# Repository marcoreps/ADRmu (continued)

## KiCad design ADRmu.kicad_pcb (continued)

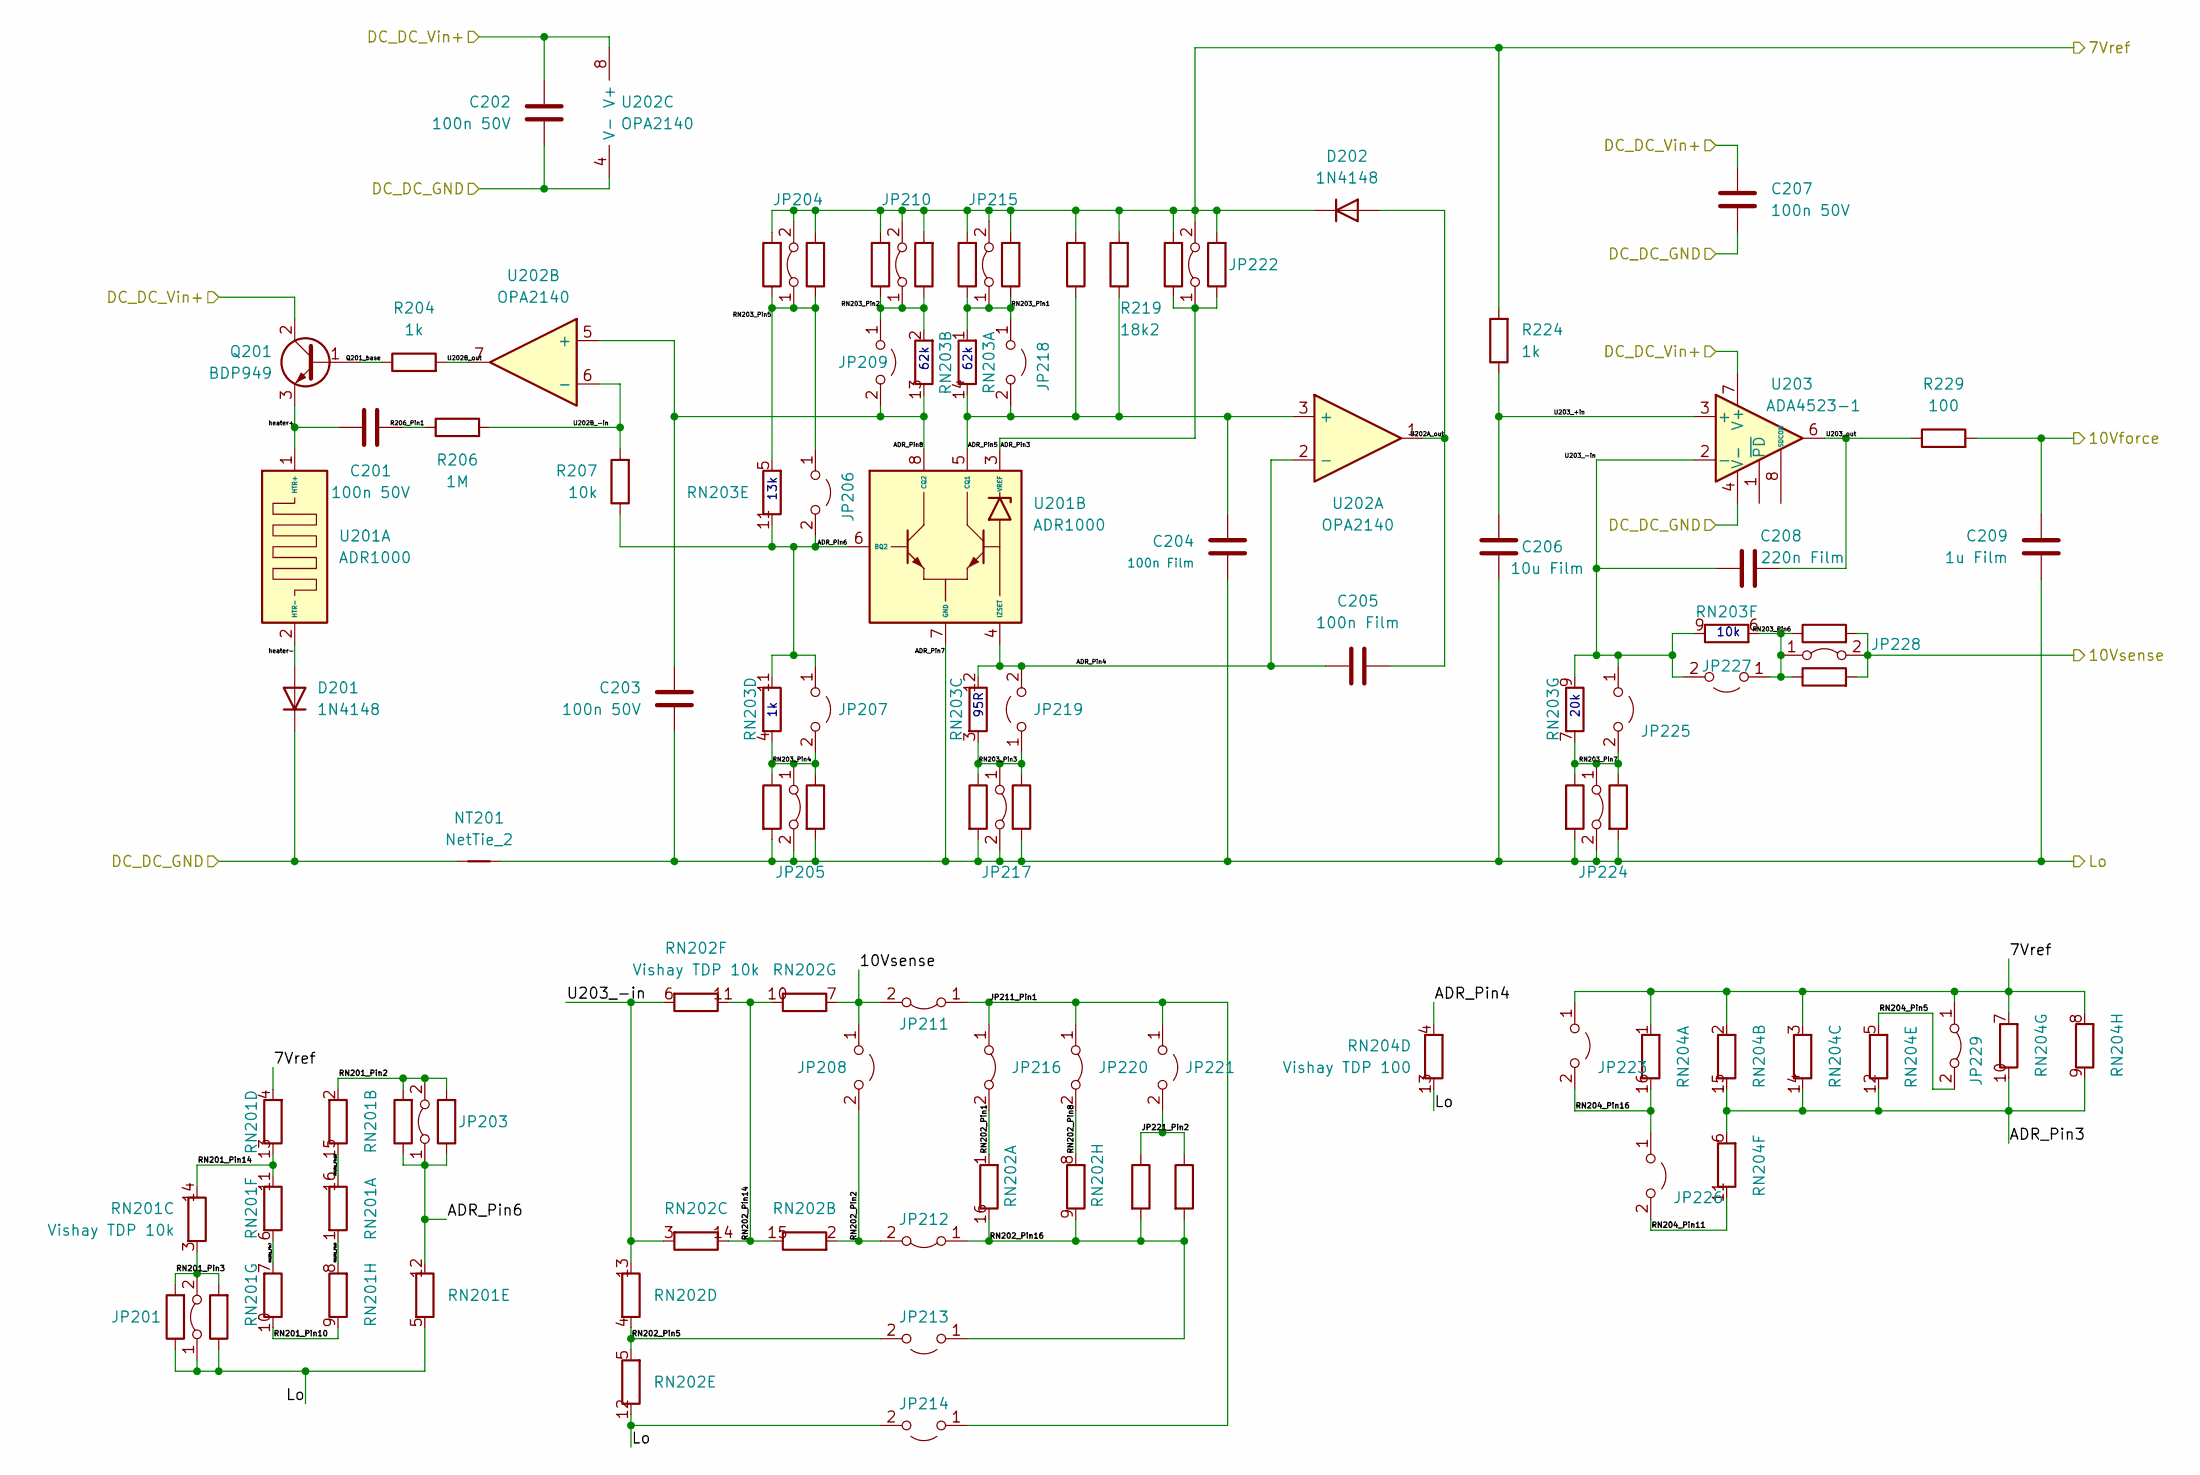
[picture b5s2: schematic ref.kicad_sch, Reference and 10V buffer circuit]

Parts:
C201, C202, C203, C207: 100n 50V; C_0805_2012Metric
C204, C205: 100n Film; C_Rect_L7.2mm_W2.5mm_P5.00mm_FKS2_FKP2_MKS2_MKP2
C206: 10u Film; C_Rect_L7.2mm_W11.0mm_P5.00mm_FKS2_FKP2_MKS2_MKP2
C208: 220n Film; C_Rect_L7.2mm_W3.0mm_P5.00mm_FKS2_FKP2_MKS2_MKP2
C209: 1u Film; C_Rect_L4.6mm_W5.5mm_P2.50mm_MKS02_FKP02
D201, D202: 1N4148; D_SOD-123
JP201, JP203, JP204, JP205, JP210, JP211, JP212, JP215, JP216, JP217, JP220, JP222, JP224, JP228, JP229: Jumper_2_Bridged; SolderJumper-2_P1.3mm_Bridged_RoundedPad1.0x1.5mm
JP206, JP207, JP208, JP209, JP213, JP214, JP218, JP219, JP221, JP223, JP225, JP226, JP227: Jumper_2_Open; SolderJumper-2_P1.3mm_Open_RoundedPad1.0x1.5mm
NT201: NetTie_2; NetTie-2_SMD_Pad0.5mm
Q201: BDP949; SOT-223-3_TabPin2
R201, R203, R209, R210, R213, R215, R216, R220, R223, R225, R228: 0; Crystal_HC52-U_Vertical
R202, R205, R208, R211, R212, R214, R217, R221, R222, R226, R227: 0; R_0805_2012Metric
R204, R224: 1k; R_0805_2012Metric
R206: 1M; R_0805_2012Metric
R207: 10k; R_0805_2012Metric
R218: 18k2; R_0805_2012Metric
R219: 18k2; Crystal_HC52-U_Vertical
R229: 100; R_0805_2012Metric
RN201, RN202: Vishay TDP 10k; DIP-16_W7.62mm
RN203: 322146; DIP-14_W7.62mm
RN204: Vishay TDP 100; DIP-16_W7.62mm
U201: ADR1000; TO-5-8
U202: OPA2140; SOIC-8_3.9x4.9mm_P1.27mm
U203: ADA4523-1; SOIC-8_3.9x4.9mm_P1.27mm

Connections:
/DC-DC/12Vf: C202.2, C207.2, Q201.2 (C), U202.8 (V+), U203.7 (V+); also elsewhere on the board
/ref/7Vref: D202.1 (K), JP204.2 (B), JP210.2 (B), JP215.2 (B), JP222.2 (B), JP223.1 (A), JP229.1 (A), R208.2, R210.2, R212.2, R213.2, R214.2, R216.2, R218.2, R219.2, R221.2, R223.2, R224.2, RN201.4 (R4.1), RN204.1 (R1.1), RN204.2 (R2.1), RN204.3 (R3.1), RN204.7 (R7.1), RN204.8 (R8.1); also elsewhere on the board
/ref/10Vforce: C209.2, R229.2; also elsewhere on the board
/ref/10Vsense: JP208.1 (A), JP211.2 (B), JP228.2 (B), R227.2, R228.2, RN202.7 (R7.1); also elsewhere on the board
/ref/ADR_Pin3: JP222.1 (A), R221.1, R223.1, RN204.6 (R6.1), RN204.9 (R8.2), RN204.10 (R7.2), RN204.12 (R5.2), RN204.14 (R3.2), RN204.15 (R2.2), U201.3 (VREF)
/ref/ADR_Pin4: C205.2, JP219.2 (B), RN203.12 (R3.2), RN204.4 (R4.1), U201.4 (IZSET), U202.2 (-)
/ref/ADR_Pin5: C204.2, JP218.2 (B), R218.1, R219.1, RN203.14 (R1.2), U201.5 (CQ1), U202.3 (+)
/ref/ADR_Pin6: JP203.1 (A), JP206.2 (B), JP207.1 (A), R203.1, R205.1, R207.1, RN201.12 (R5.2), RN203.11 (R5.2), U201.6 (BQ2)
/ref/ADR_Pin7: C203.1, C204.1, C206.2, C209.1, JP201.1 (A), JP205.2 (B), JP214.2 (B), JP217.2 (B), JP224.2 (B), NT201.2, R201.1, R202.1, R209.2, R211.2, R215.2, R217.2, R225.2, R226.2, RN201.5 (R5.1), RN202.12 (R5.2), RN204.13 (R4.2), U201.7 (GND); also elsewhere on the board
/ref/ADR_Pin8: C203.2, JP209.2 (B), RN203.13 (R2.2), U201.8 (CQ2), U202.5 (+)
/ref/JP211_Pin1: JP211.1 (A), JP214.1 (A), JP216.1 (A), JP220.1 (A), JP221.1 (A)
/ref/JP221_Pin2: JP221.2 (B), R220.1, R222.1
/ref/Q201_base: Q201.1 (B), R204.1
/ref/R206_Pin1: C201.2, R206.1
/ref/RN201_Pin2: JP203.2 (B), R203.2, R205.2, RN201.2 (R2.1)
/ref/RN201_Pin3: JP201.2 (B), R201.2, R202.2, RN201.3 (R3.1)
/ref/RN201_Pin7: RN201.6 (R6.1), RN201.7 (R7.1)
/ref/RN201_Pin8: RN201.1 (R1.1), RN201.8 (R8.1)
/ref/RN201_Pin10: RN201.9 (R8.2), RN201.10 (R7.2)
/ref/RN201_Pin14: RN201.11 (R6.2), RN201.13 (R4.2), RN201.14 (R3.2)
/ref/RN201_Pin16: RN201.15 (R2.2), RN201.16 (R1.2)
/ref/RN202_Pin1: JP216.2 (B), RN202.1 (R1.1)
/ref/RN202_Pin2: JP208.2 (B), JP212.2 (B), RN202.2 (R2.1)
/ref/RN202_Pin5: JP213.2 (B), RN202.4 (R4.1), RN202.5 (R5.1)
/ref/RN202_Pin8: JP220.2 (B), RN202.8 (R8.1)
/ref/RN202_Pin14: RN202.10 (R7.2), RN202.11 (R6.2), RN202.14 (R3.2), RN202.15 (R2.2)
/ref/RN202_Pin16: JP212.1 (A), JP213.1 (A), R220.2, R222.2, RN202.9 (R8.2), RN202.16 (R1.2)
/ref/RN203_Pin1: JP215.1 (A), JP218.1 (A), R214.1, R216.1, RN203.1 (R1.1)
/ref/RN203_Pin2: JP209.1 (A), JP210.1 (A), R212.1, R213.1, RN203.2 (R2.1)
/ref/RN203_Pin3: JP217.1 (A), JP219.1 (A), R215.1, R217.1, RN203.3 (R3.1)
/ref/RN203_Pin4: JP205.1 (A), JP207.2 (B), R209.1, R211.1, RN203.4 (R4.1)
/ref/RN203_Pin5: JP204.1 (A), JP206.1 (A), R208.1, R210.1, RN203.5 (R5.1)
/ref/RN203_Pin6: JP227.1 (A), JP228.1 (A), R227.1, R228.1, RN203.6 (R6.1)
/ref/RN203_Pin7: JP224.1 (A), JP225.2 (B), R225.1, R226.1, RN203.7 (R7.1)
/ref/RN204_Pin5: JP229.2 (B), RN204.5 (R5.1)
/ref/RN204_Pin11: JP226.2 (B), RN204.11 (R6.2)
/ref/RN204_Pin16: JP223.2 (B), JP226.1 (A), RN204.16 (R1.2)
/ref/U202A_out: C205.1, D202.2 (A), U202.1
/ref/U202B_-in: R206.2, R207.2, U202.6 (-)
/ref/U202B_out: R204.2, U202.7
/ref/U203_+in: C206.1, R224.1, U203.3 (+)
/ref/U203_-in: C208.2, JP225.1 (A), JP227.2 (B), RN202.3 (R3.1), RN202.6 (R6.1), RN202.13 (R4.2), RN203.9 (R6.2), U203.2 (-)
/ref/U203_out: C208.1, R229.1, U203.6
/ref/heater+: C201.1, Q201.3 (E), U201.1 (HTR+)
/ref/heater-: D201.2 (A), U201.2 (HTR-)
GNDA: C202.1, C207.1, D201.1 (K), NT201.1, U202.4 (V-), U203.4 (V-); also elsewhere on the board

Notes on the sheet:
20k
10k
62k
95R
13k

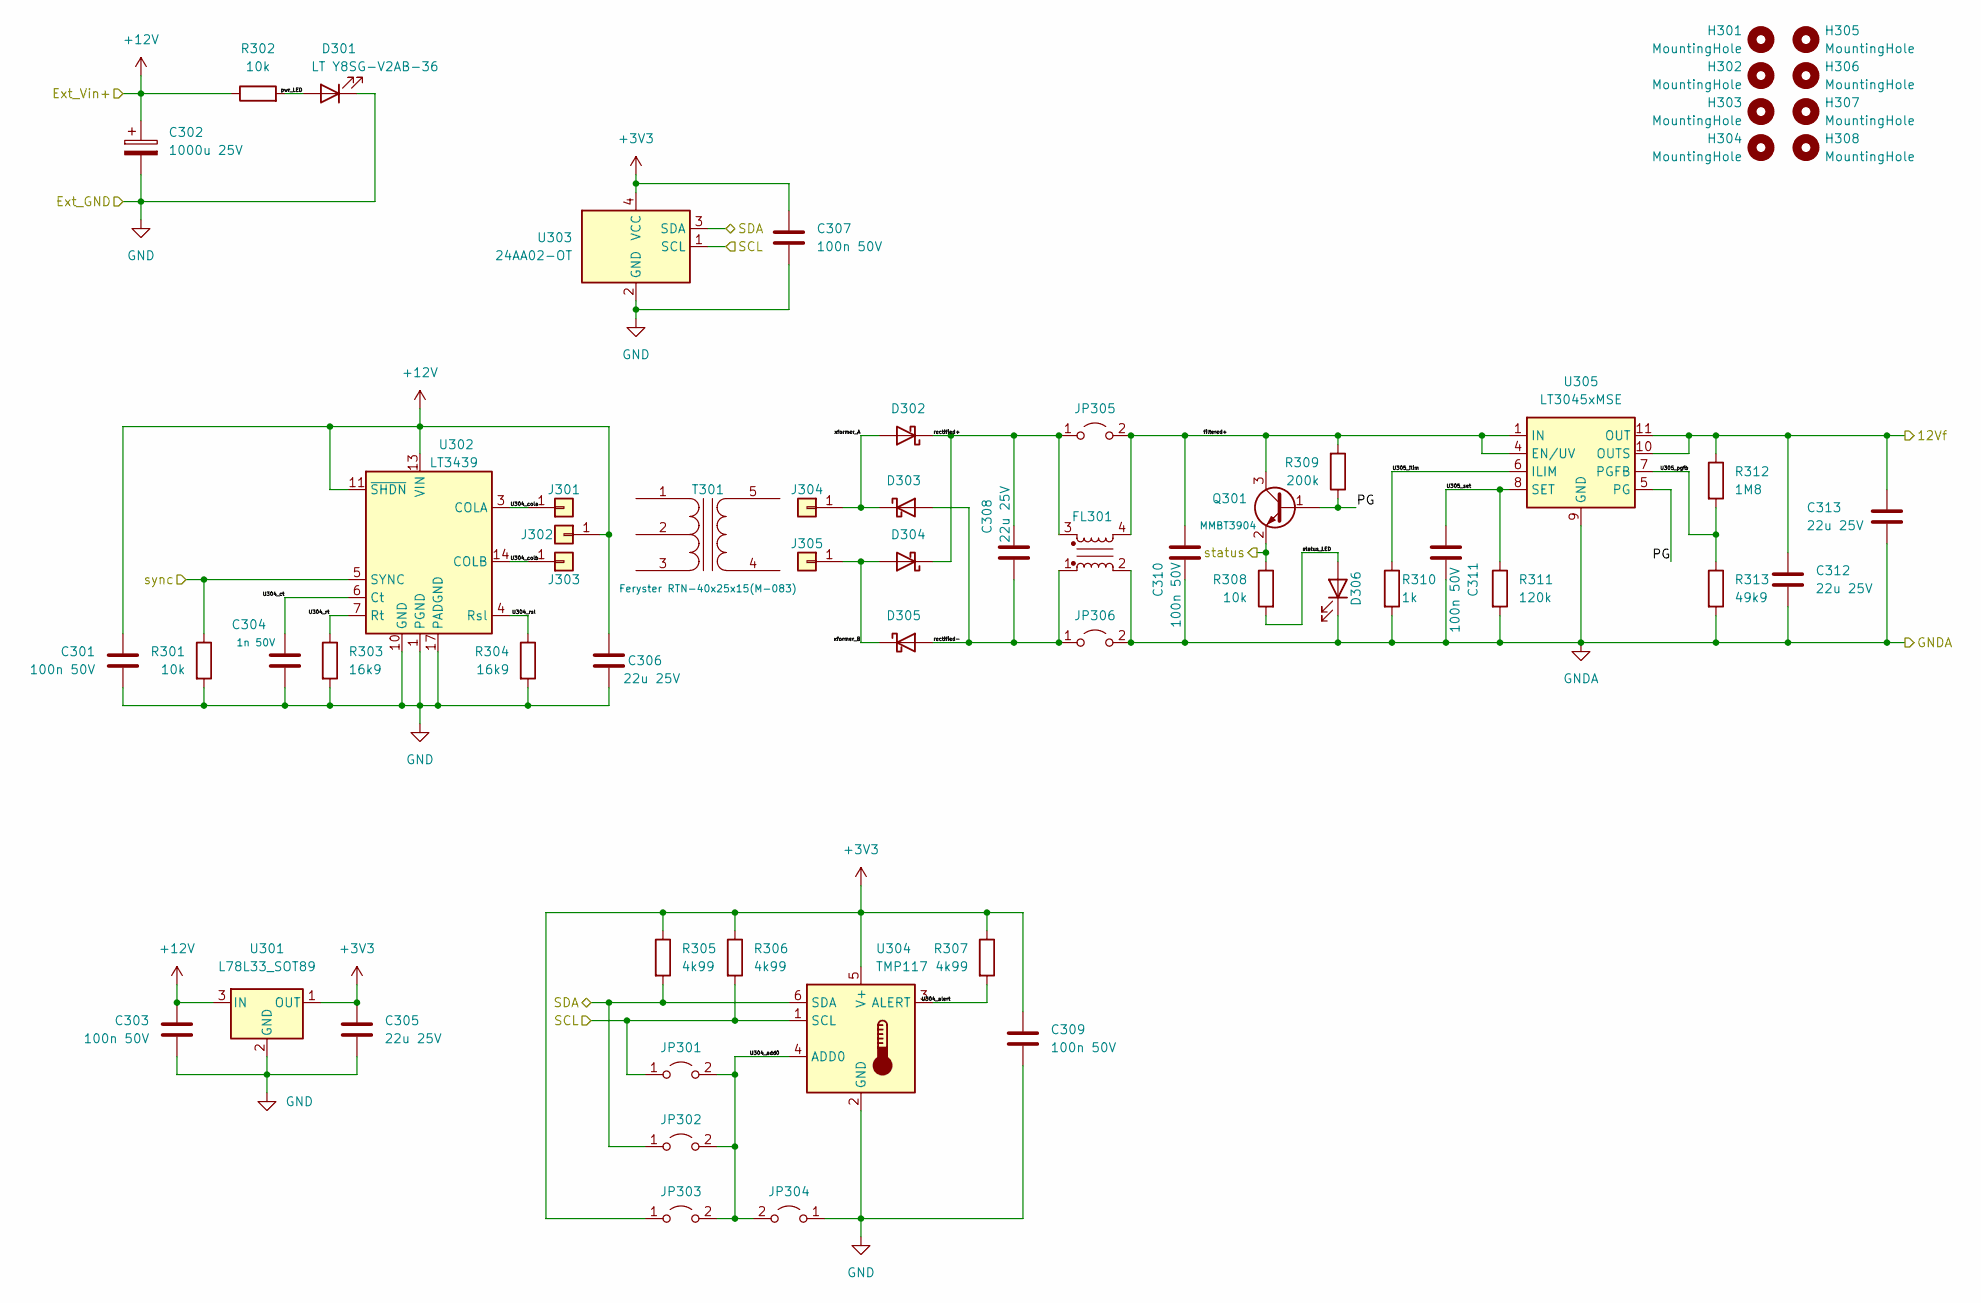
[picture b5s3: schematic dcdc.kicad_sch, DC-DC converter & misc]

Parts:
C301, C303, C307, C309, C310, C311: 100n 50V; C_0805_2012Metric
C302: 1000u 25V; CP_Radial_D16.0mm_P7.50mm
C304: 1n 50V; C_0805_2012Metric
C305, C306, C308, C312, C313: 22u 25V; C_1206_3216Metric
D301, D306: LT Y8SG-V2AB-36; LED_1206_3216Metric
D302, D303, D304, D305: PMEG6010CEH; D_SOD-123F
FL301: B82793C0206N265; Filter_EPCOS_B82793C0
H301, H302, H303, H304, H305, H306, H307, H308: MountingHole; MountingHole_4.3mm_M4
J301, J302, J303, J304, J305: Conn_01x01; SolderWire-1sqmm_1x01_D1.4mm_OD3.9mm
JP301, JP302, JP303, JP304, JP305, JP306: Jumper_2_Open; SolderJumper-2_P1.3mm_Open_RoundedPad1.0x1.5mm
Q301: MMBT3904; SOT-23
R301, R302, R308: 10k; R_0805_2012Metric
R303, R304: 16k9; R_0805_2012Metric
R305, R306, R307: 4k99; R_0805_2012Metric
R309: 200k; R_0805_2012Metric
R310: 1k; R_0805_2012Metric
R311: 120k; R_0805_2012Metric
R312: 1M8; R_0805_2012Metric
R313: 49k9; R_0805_2012Metric
T301: Feryster RTN-40x25x15(M-083)
U301: L78L33_SOT89; SOT-89-3
U302: LT3439; TSSOP-16-1EP_4.4x5mm_P0.65mm
U303: 24AA02-OT; SOT-23-5
U304: TMP117; WSON-6-1EP_2x2mm_P0.65mm_EP1x1.6mm
U305: LT3045xMSE; MSOP-12-1EP_3x4mm_P0.65mm_EP1.65x2.85mm

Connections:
+3V3: C305.1, C307.1, C309.1, JP303.1 (A), R305.1, R306.1, R307.1, U301.1 (OUT), U303.4 (VCC), U304.5 (V+)
+12V: C301.1, C302.1, C303.1, C306.1, J302.1, R302.1, U301.3 (IN), U302.11 (~SHDN), U302.13 (VIN); also elsewhere on the board
/DC-DC/12Vf: C312.1, C313.1, R312.1, U305.10 (OUTS), U305.11 (OUT), U305.12 (OUT); also elsewhere on the board
/DC-DC/PG: Q301.1 (B), R309.1, U305.5 (PG)
/DC-DC/SCL: JP301.1 (A), R306.2, U303.1 (SCL), U304.1 (SCL); also elsewhere on the board
/DC-DC/SDA: JP302.1 (A), R305.2, U303.3 (SDA), U304.6 (SDA); also elsewhere on the board
/DC-DC/U304_add0: JP301.2 (B), JP302.2 (B), JP303.2 (B), JP304.2 (B), U304.4 (ADD0)
/DC-DC/U304_alert: R307.2, U304.3 (ALERT)
/DC-DC/U304_cola: J301.1, U302.3 (COLA)
/DC-DC/U304_colb: J303.1, U302.14 (COLB)
/DC-DC/U304_ct: C304.1, U302.6 (Ct)
/DC-DC/U304_rsl: R304.1, U302.4 (Rsl)
/DC-DC/U304_rt: R303.1, U302.7 (Rt)
/DC-DC/U305_ilim: R310.1, U305.6 (ILIM)
/DC-DC/U305_pgfb: R312.2, R313.1, U305.7 (PGFB)
/DC-DC/U305_set: C311.1, R311.1, U305.8 (SET)
/DC-DC/filtered+: C310.1, FL301.4, JP305.2 (B), Q301.3 (C), R309.2, U305.1 (IN), U305.2 (IN), U305.3 (IN), U305.4 (EN/UV)
/DC-DC/pwr_LED: D301.2 (A), R302.2
/DC-DC/rectified+: C308.1, D302.1 (K), D304.1 (K), FL301.3, JP305.1 (A)
/DC-DC/rectified-: C308.2, D303.2 (A), D305.2 (A), FL301.1, JP306.1 (A)
/DC-DC/status: Q301.2 (E), R308.1; also elsewhere on the board
/DC-DC/status_LED: D306.2 (A), R308.2
/DC-DC/sync: R301.1, U302.5 (SYNC); also elsewhere on the board
/DC-DC/xformer_A: D302.2 (A), D303.1 (K), J304.1
/DC-DC/xformer_B: D304.2 (A), D305.1 (K), J305.1
GND: C301.2, C302.2, C303.2, C304.2, C305.2, C306.2, C307.2, C309.2, D301.1 (K), JP304.1 (A), R301.2, R303.2, R304.2, U301.2 (GND), U302.1 (PGND), U302.10 (GND), U302.16 (PGND), U302.17 (PADGND), U303.2 (GND), U304.2 (GND); also elsewhere on the board
GNDA: C310.2, C311.2, C312.2, C313.2, D306.1 (K), FL301.2, JP306.2 (B), R310.2, R311.2, R313.2, U305.9 (GND), U305.13 (GND); also elsewhere on the board

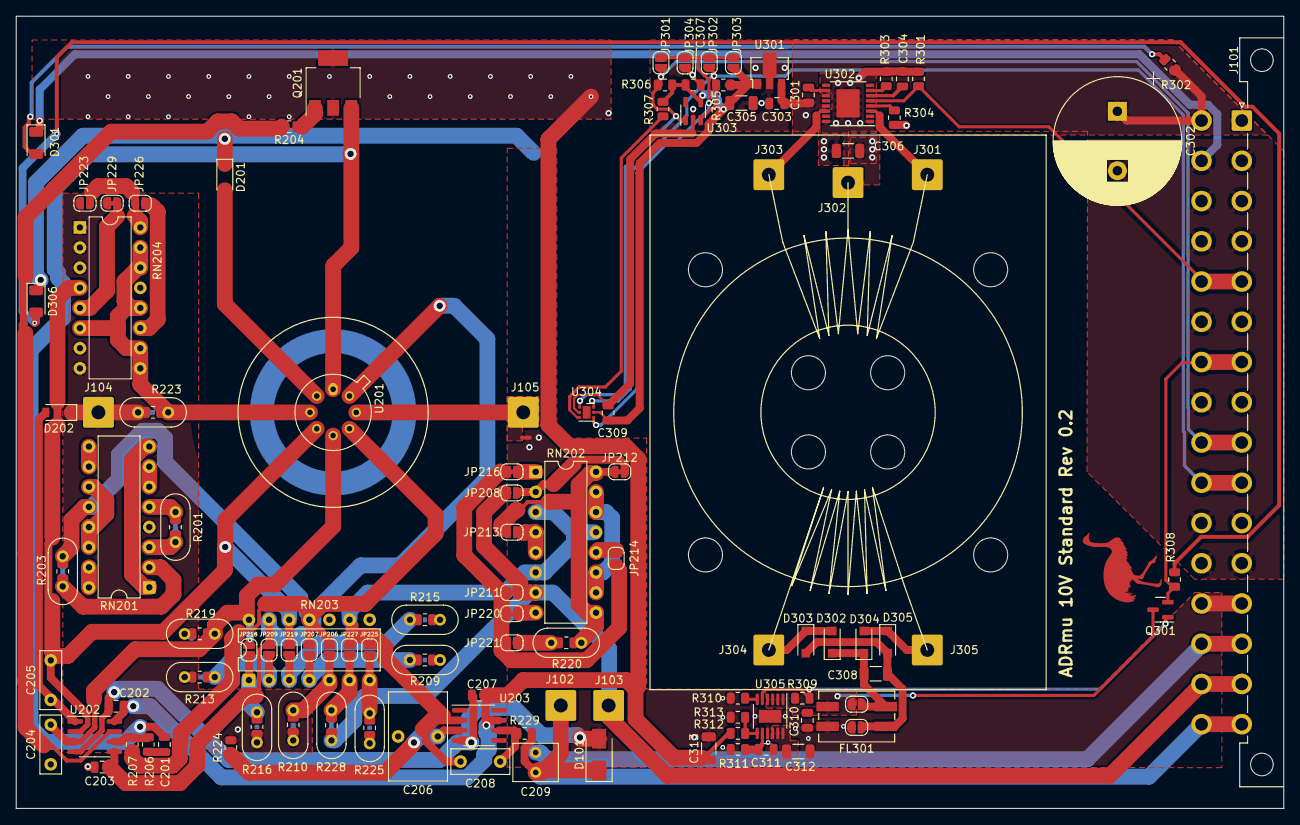
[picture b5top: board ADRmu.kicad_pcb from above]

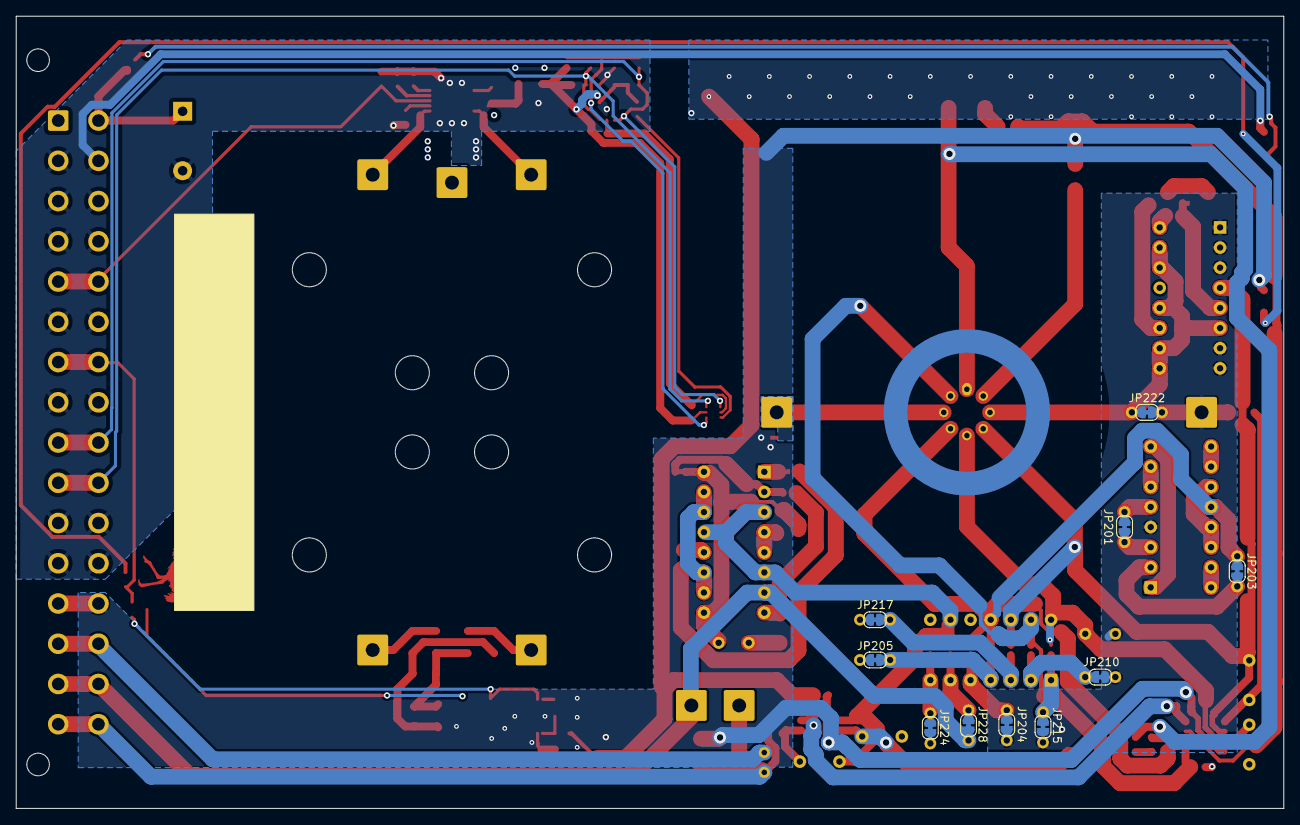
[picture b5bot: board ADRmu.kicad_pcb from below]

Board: 4 copper layers, 160.0 x 100.0 mm, 142 parts (10 on the bottom side), 71 nets.

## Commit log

2022-01-09 asdf
2022-01-10 added i2c temperature sensor and eeprom
2022-01-11 asas
2022-01-12 started proto area
2022-01-12 added 10V buffer
2022-01-12 the small reset
2022-01-12 ASDF!
2022-01-13 asdf?
2022-01-13 getting there ...
2022-01-13 send halp
2022-01-13 net classes
2022-01-13 trace widths based on net classes
2022-01-14 flood of prototyping area
2022-01-14 reference designators reassigned
2022-01-14 added common mode filter
2022-01-14 generated bom, pdf, gerbers
2022-01-14 added README and rendered image
2022-01-14 added some dubious copper rings
2022-01-14 added dubious flightless birb
2022-01-30 Obligatory bugs in the first production run:
    - Missing stability cap between buffer out and -in
    - Missing cap for autozeroing buffer
    - Side status LEDs need to be flipped
    - Many schematic net names wrong
    - LDO power good implemented wrong
2022-02-01 GNDf terminal was sharing a via with heater return
2022-02-02 schematics updated to rev.2
2022-02-03 extended README
2022-02-04 added 24h ppm plot
2022-02-04 added xml bom
2022-02-10 adding prec resistor alternatives
2022-02-11 goodbye proto area, hello resistor networks
2022-02-11 Rev 0.3
2022-02-11 new folder structure to accommodate battery module
2022-02-12 switched to addressable eeprom
2022-02-12 I shall waste not a copper
2022-02-12 rs-274x gerbers
2022-02-12 started battery module
2022-02-13 backplane connector changes
2022-02-14 Battery charger Rev 0.1 finished
2022-02-18 started Rev. 0.4 with better 1k/12k divider
2022-02-28 new TODOs after rev. 3 board assembly -_-
2022-03-03 rev 0.4 layout step
2022-03-03 rev 0.4 layout done
2022-03-17 45445
2022-03-28 dimmed LED brightness and started to fix a few first generation battery bug fixes
2022-03-31 adds eeprom script + TMP117 address config aid
2022-04-07 Battery module Rev 0.2
2022-04-09 Lowered Vreg to 11V to keep things cooler
2022-05-16 prepared rev 0.3 battery module with fuel gauge
2022-05-16 battery module rev 0.3 routed
2022-05-22 Reference board Rev 0.5 schematic
2022-05-23 Rev 0.5 routed
2022-05-23 No longer configured for PRND by default
2022-06-03 minor bug fixes for battery module
2022-06-04 Battery module Rev 0.4 routed
2022-07-11 Battery module Rev 0.6 update
2022-08-15 New backplane, Reference Rev 0.6 with heated resistor network support
2022-08-23 Rev 0.2 Backplane
2022-12-27 Ref module Rev. 0.9
2023-01-01 restructures the folders and adds READMEs
2023-01-01 adds cost estimate csv
2023-01-09 12345
2023-01-20 ADRmu illustrated statistics
2023-01-29 Rev. 1.0
2023-02-01 New noise results
2023-02-01 Noice
2023-02-01 nose
2023-02-01 more less noise
2023-02-05 corrected noise measurements
2023-02-08 remade some noise measurements
2023-02-17 Rev 1.1 & Kicad 7 update
2023-02-19 Remade all 0.1 ... 10 Hz noise tests with new preamp
2023-03-09 Rev 1.2
2024-02-24 fresh results
2024-02-25 One ADRmu vs average of many 1 year plot
